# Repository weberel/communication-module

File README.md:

# ecoTrace Communication Module

> ## 🚧 HARDWARE VALIDATED, APPLICATION NOT YET - read this
> As of the **2026-08-06/07** bring-up campaign the **board is fully validated on
> real hardware**: both charge inputs (USB and solar, incl. VINDPM/MPPT control),
> cellular, WiFi, all I2C sensors, the SPI flash, deep sleep, and the QON button
> (wake / OTA mode / ship-mode power-off). GPS is the only untested block.
> The `lib/EcoTrace` drivers underneath all of that ran on hardware too.
>
> What has **NOT been exercised end-to-end** is the **`datalogger` application
> itself**: the 5-minute duty cycle, the flash ring log across power loss, MPPT
> tracking over a real day, the twice-daily ThingsBoard upload with clock sync,
> and watchdog/crash recovery. It compiles and boots; treat it as a scaffold to
> validate, not as proven.
>
> Full breakdown, including the measured numbers: [`docs/testing-status.md`](docs/testing-status.md).

Firmware and board-support for the **ecoTrace Communication Module** - a small,
battery- and solar-powered ESP32-C6 board with an LTE modem, built for **logging
data remotely** from the field.

This repo gives you a ready-to-run **datalogger** plus a library of drop-in
**functions for every peripheral** on the board, so you can fork the logger and add
whatever you need. It is the starting point for anyone (students, collaborators)
picking up the board.

> ⚠️ **Read [`docs/hardware-errata.md`](docs/hardware-errata.md) before wiring anything.**
> Rev A has a **swapped VIN +/- silkscreen** and other gotchas.

---

## The board at a glance

| | |
|---|---|
| MCU | ESP32-C6-MINI-1 (WiFi / BLE / 802.15.4, native USB Serial/JTAG) |
| Power / charging | **BQ25792** buck-boost charger + PMIC - USB, solar (MPPT), LiPo, 16-bit ADC |
| Cellular | **SIMCom A7672E-LASE** LTE Cat-1 modem (+ internal GNSS, untested) |
| Sensors (optional) | SC7A20 accelerometer, LTR-303ALS ambient light |
| Storage | GD25Q128 16 MB SPI NOR flash |
| Security | ATECC608B secure element |
| Inputs | USB-C (power + flashing), SIM slot, battery connector, VIN (solar/DC in) |
| Antennas | u.FL for LTE and GPS |

Board revision: **Rev A, 2026-04-23**. Full KiCad project, schematic PDF, board
renders, and JLCPCB fab files are in [`hardware/`](hardware/).

## What you get

**1. The datalogger** (`src/datalogger/`) - the main application. Every 5-minute
wake it:
- reads the full battery + charger state (BQ25792) and the I2C sensors
  (LTR-303 light, SC7A20 accel, MS5837 pressure + temperature on the hat header),
- runs a solar-management pass: **MPPT** (fractional-Voc + perturb-&-observe on
  VINDPM) to maximise input power, per-day **harvest accounting**, and a
  **weather-adaptive charge target** - good weather caps charging at ~80 % SoC to
  age the LiPo slower, bad weather allows 100 % for reserve,
- appends one 64-byte record to a **ring log on the 16 MB SPI flash**
  (power-loss safe, ~2.5 years of capacity),
- twice a day drains the backlog to **ThingsBoard** in timestamped batches -
  cellular first, **WiFi as backup** - and syncs the wall clock from the network,
- deep-sleeps in between with everything powered down (modem rail, flash,
  sensors, charger ADC); the BQ25792 keeps charging autonomously.

It is a **hackable starting point** - fork it and change whatever you need. To log
your own sensor: extend `LogRecord` in [`record.h`](src/datalogger/record.h) (spare
bytes are reserved), read it in `readSample()` in
[`main.cpp`](src/datalogger/main.cpp), and send it in `recordValues()` in
[`uplink.cpp`](src/datalogger/uplink.cpp). Connect external sensors on the SENSOR
(I2C) or SPI header. Tune the duty cycle / charge profile / MPPT / weather
thresholds in [`config.h`](src/datalogger/config.h).

**2. The driver library** (`lib/EcoTrace/`) - ready-to-call functions for every part
on the board. Pull in only what you need. Full list: [`docs/api-reference.md`](docs/api-reference.md).

| Driver | Covers | Status |
|--------|--------|--------|
| `BQ25792` | charging (USB + solar), ADC, status, faults, MPPT/VINDPM | ✅ full, datasheet-accurate |
| `ModemA7672` | LTE power/AT, SIM, registration, GPRS, HTTP GET/POST, time | ✅ full (GPS = stub) |
| `LTR303` | ambient light (CH0/CH1, lux) - datalogger's example sensor | ✅ |
| `SC7A20` | accelerometer (X/Y/Z mg) | ✅ |
| `ExtFlash` | GD25Q128 read/erase/program, power-down | ✅ (full 16 MB) |
| `MS5837` | MS5837-02BA barometer (pressure, temperature, altitude) | ✅ |
| `ATECC608B` | secure element presence/wake | 🔹 thin (crypto via CryptoAuthLib) |
| `EcoTraceBoard` | safe init, I2C/SPI bring-up, deep sleep | ✅ |

**3. The board self-test** (`src/functionality_test/`) - probes every device and
prints a `PASS / FAIL / SKIP` report. Run it first on a new board.

## Toolchain

**VS Code + PlatformIO + Arduino-ESP32.** Reproducible builds, a real editor, the
Arduino library ecosystem, and full ESP-IDF APIs underneath when needed. See
[`docs/getting-started.md`](docs/getting-started.md).

The ESP32-C6 needs arduino-esp32 v3+, which the official PlatformIO platform does not
ship yet - this project pins the [pioarduino](https://github.com/pioarduino/platform-espressif32)
fork (version `53.03.13`) in `platformio.ini`. Don't unpin it.

## Quick start

```bash
# 1. open this folder in VS Code with the PlatformIO extension installed
# 2. plug the board in over USB-C (keep a battery connected -- see errata)
# 3. check the board is healthy:
pio run -e functionality_test -t upload && pio device monitor

# 4. set your SIM APN + upload URL, then run the logger:
cp lib/EcoTrace/secrets.example.h lib/EcoTrace/secrets.h   # then edit it
pio run -e datalogger -t upload && pio device monitor

# 5. reflash over WiFi later (bench convenience): press the QON button 3x
#    (board joins WiFi, blinks once per second, prints its IP on serial), then:
pio run -e datalogger        # build the new image
curl -F "image=@.pio/build/datalogger/firmware.bin" http://<board-ip>/update
#    (espota / `pio run -e datalogger_ota -t upload` also exists but its UDP
#     handshake proved unreliable on real networks -- prefer the curl path)
```

Without a `POST_URL` in `secrets.h` the datalogger runs in bench mode: it samples and
prints over serial but does not transmit.

## Layout

```
lib/EcoTrace/      board support: pin map + drivers (the reusable core)
  ecotrace_pins.h    single source of truth for the pin map
  EcoTraceBoard.*    safe init, I2C/SPI bring-up, deep-sleep helper
  BQ25792.*          charger / PMIC (hand-written, datasheet-accurate)
  ModemA7672.*       LTE modem (hand-written AT stack)
  LTR303.* SC7A20.* ATECC608B.* ExtFlash.*   peripheral drivers
  secrets.example.h  copy to secrets.h and fill in (gitignored)
src/
  datalogger/        the main application
    config.h           duty cycle, charge profile, MPPT, weather, upload tunables
    record.h           the 64-byte on-flash log record (+ CRC)
    flash_log.*        power-loss-safe ring log on the 16 MB SPI flash
    solar.*            MPPT + harvest tracking + weather-adaptive charge target
    uplink.*           ThingsBoard upload: cellular first, WiFi backup, clock sync
    main.cpp           the wake/sample/sleep cycle
  functionality_test/  board bring-up self-test
docs/              getting started, pinout, errata, api reference, testing status
hardware/          KiCad project + exports
```

## Related

- `functionality_test_arduino` - the original bring-up test this repo grew from.
- `bms_stove` - an ESP-IDF application on this hardware (remote battery/stove
  datalogger), a reference for a full deployment.

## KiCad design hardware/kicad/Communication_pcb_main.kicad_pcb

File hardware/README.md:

# Hardware

The KiCad design and manufacturing outputs for the ecoTrace Communication Module
(Rev A, 2026-04-23) are included here so you don't need Drive access.

```
hardware/
  kicad/         KiCad project - open Communication_pcb_main.kicad_pro in KiCad
    Communication_pcb_main.kicad_pro / .kicad_pcb / .kicad_sch
    mcu.kicad_sch  power_mgmt.kicad_sch  simcom.kicad_sch   (schematic sheets)
    jlcpcb/        fab outputs: gerbers, drill, BOM, CPL, GERBER-*.zip
  exports/       viewable without KiCad:
    Communication_pcb_main-schematic.pdf
    board-top.png  board-bottom.png   (3D renders)
```

## No KiCad? Start here

- **Schematic:** `exports/Communication_pcb_main-schematic.pdf`. Sheets: `mcu`,
  `power_mgmt`, `simcom`. The **power_mgmt** sheet (BQ25792) is the one to know: it
  defines the charging path, VSYS, the NTC (TS) network (note the errata), and the
  ACDRV FET gating for USB vs solar inputs.
- **Board:** `exports/board-top.png` / `board-bottom.png`.

## Fabrication

`kicad/jlcpcb/` holds a ready-to-order set (gerbers, drill, BOM, CPL, and a zipped
gerber bundle) targeted at JLCPCB. Re-export from KiCad if you change the board.

This is the **current 4-layer** version of the board (F.Cu / In1 / In2 / B.Cu). An
older 2-layer design also exists on the shared drive; it is not included here.

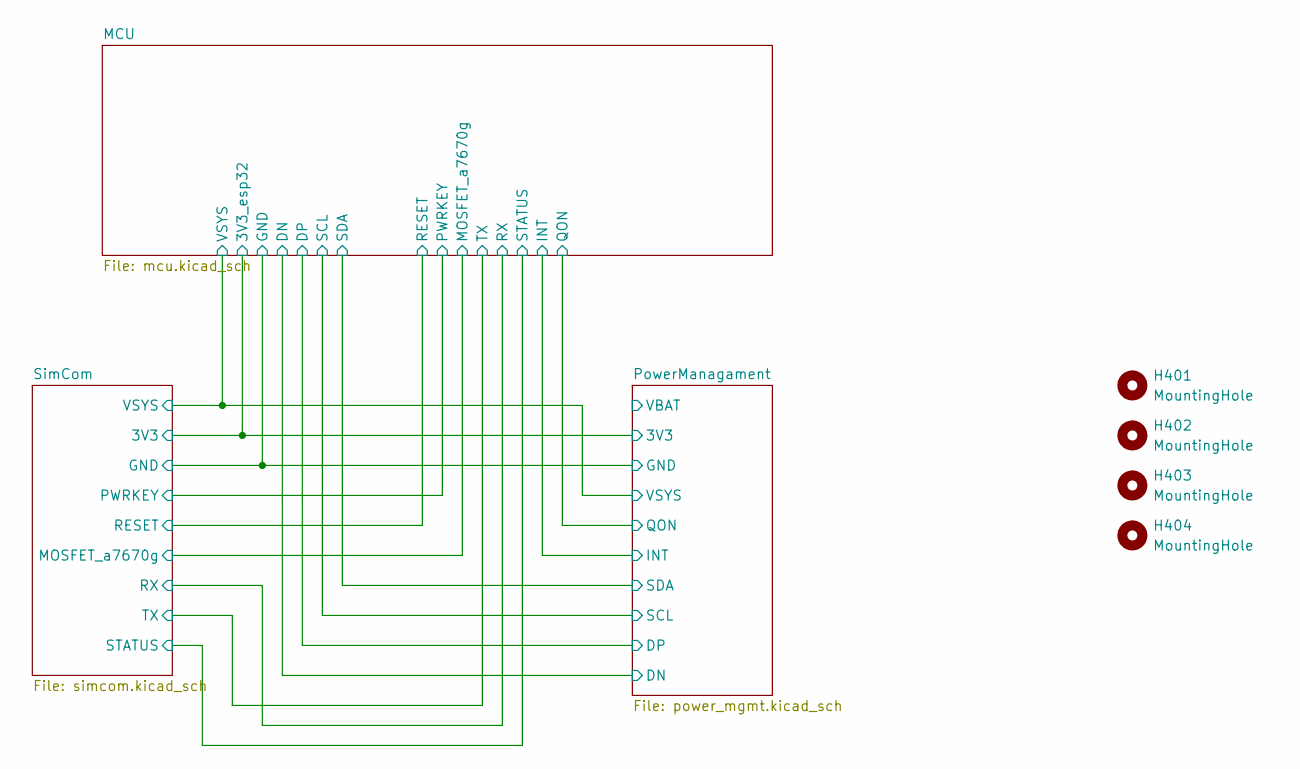
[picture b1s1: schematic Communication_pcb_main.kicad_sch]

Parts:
H401, H403: MountingHole; MountingHole_2.2mm_M2_ISO14580_Pad
H402, H404: MountingHole; Slot_2.2mm_M2_ISO14580_Pad

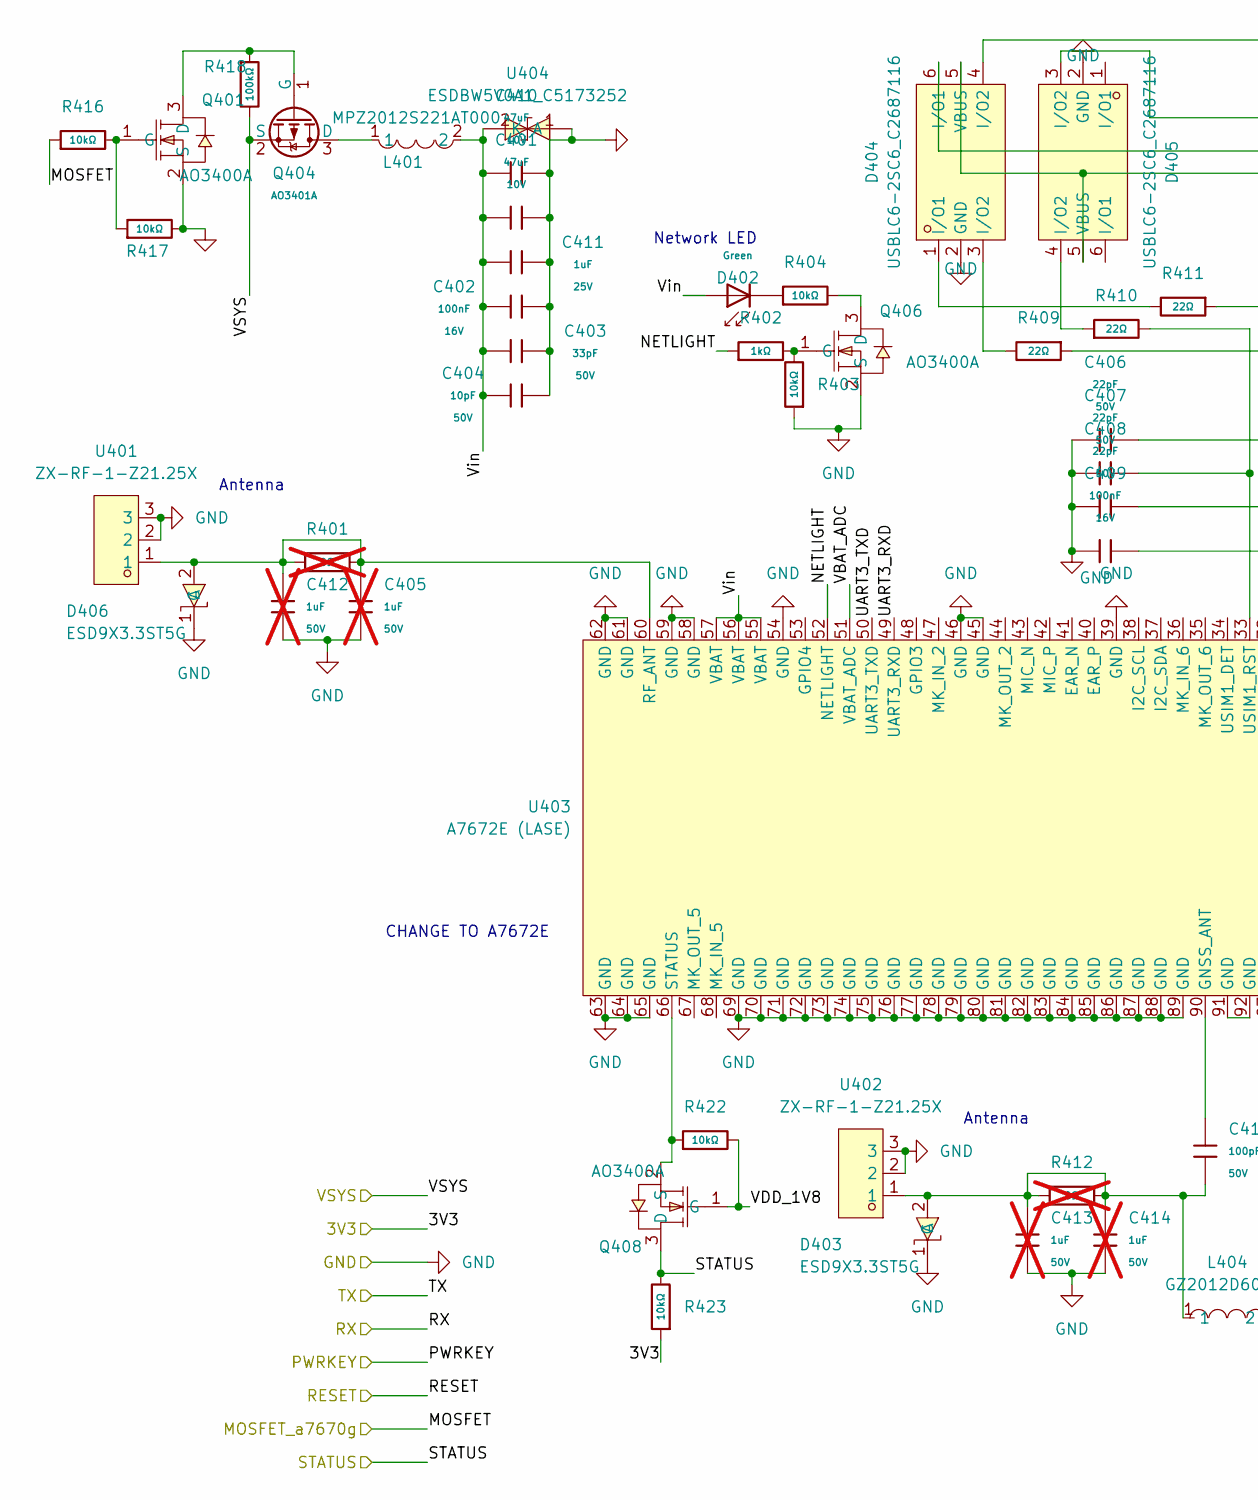
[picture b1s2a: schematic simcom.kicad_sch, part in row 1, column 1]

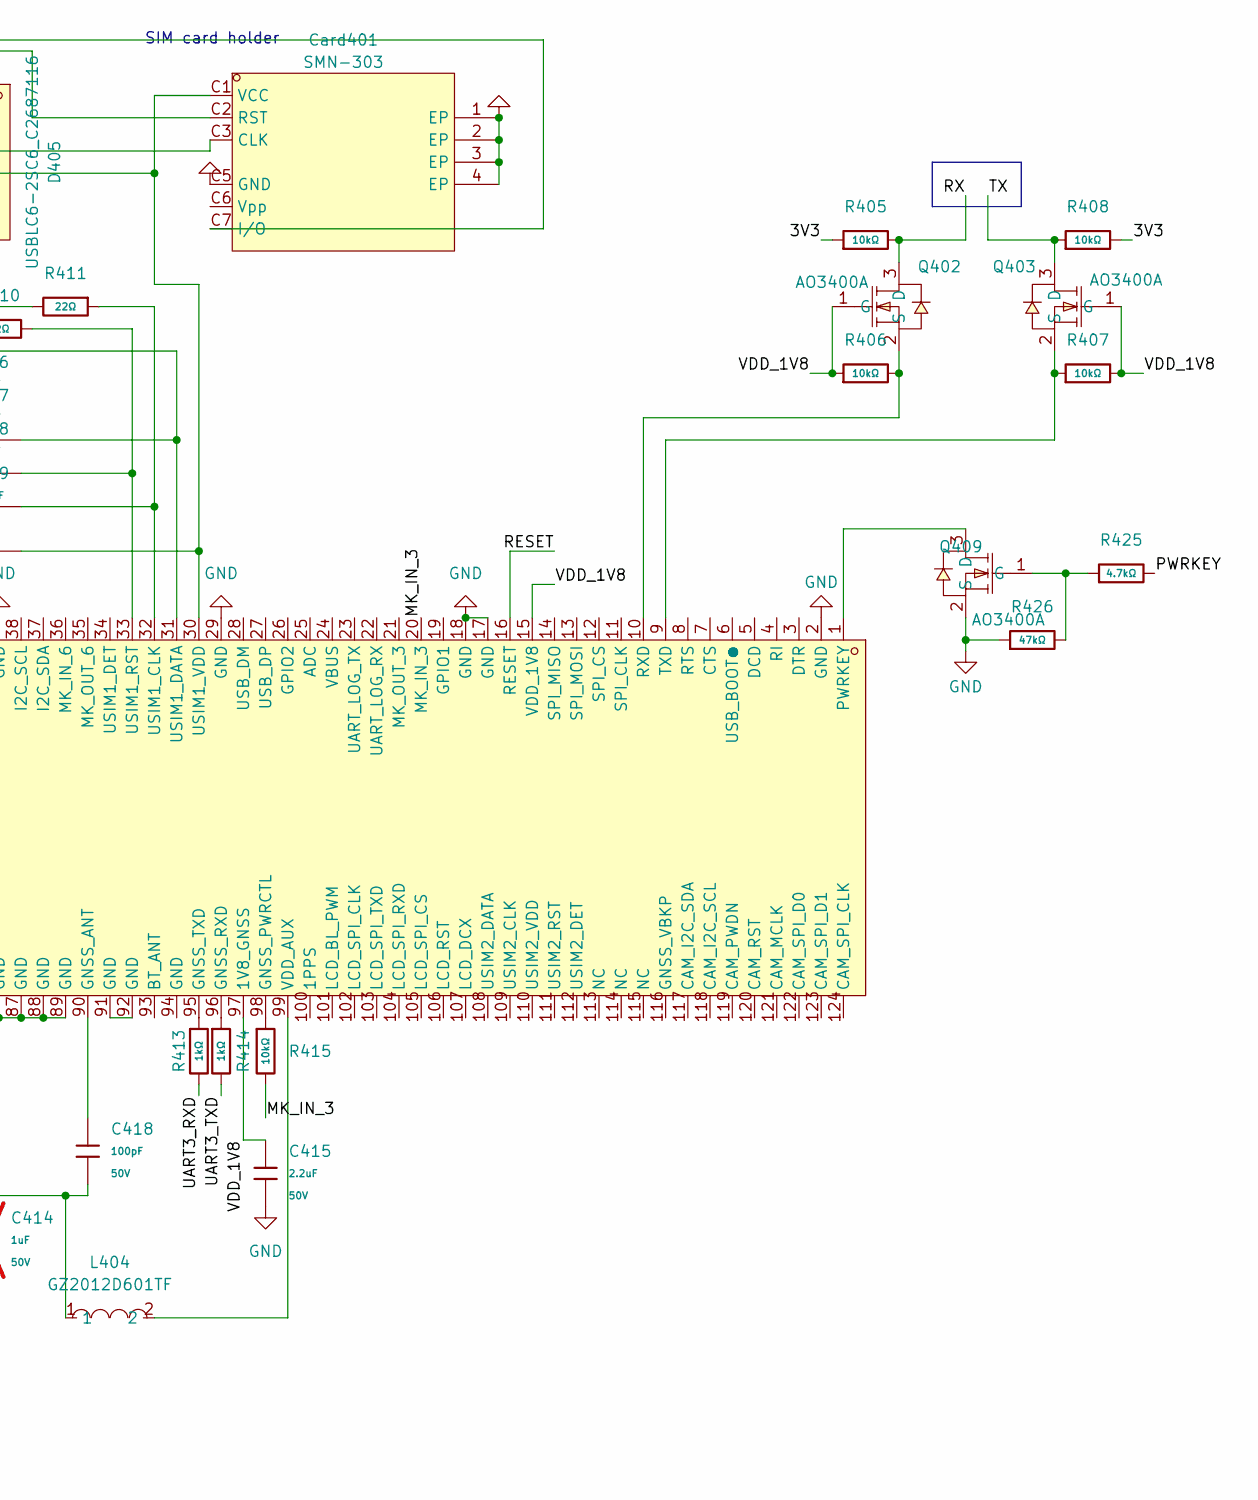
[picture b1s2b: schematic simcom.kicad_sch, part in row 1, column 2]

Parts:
C401, C410: 47uF; C_1206; Voltage Rated 10V; Tolerance ±20%; Part CL31A476MPHNNNE; LCSC C96123
C402, C409: 100nF; C_0402; Voltage Rated 16V; Tolerance ±10%; Part CL05B104KO5NNNC; LCSC C1525
C403: 33pF; C_0402; Voltage Rated 50V; Tolerance ±5%; Part 0402CG330J500NT; LCSC C1562
C404: 10pF; C_0402; Voltage Rated 50V; Tolerance ±5%; Part CL05C100JB5NNNC; LCSC C32949
C405, C412, C413, C414: 1uF; C_0805; Voltage Rated 50V; Tolerance ±10%; Part CL21B105KBFNNNE; LCSC C28323; not fitted
C406, C407, C408: 22pF; C_0402; Voltage Rated 50V; Tolerance ±5%; Part 0402CG220J500NT; LCSC C1555
C411: 1uF; C_0402; Voltage Rated 25V; Tolerance ±10%; Part CL05A105KA5NQNC; LCSC C52923
C415: 2.2uF; C_0805; Voltage Rated 50V; Tolerance ±10%; Part CL21A225KBQNNNE; LCSC C377773
C418: 100pF; C_0805; Voltage Rated 50V; Tolerance ±5%; Part CL21C101JBANNNC; LCSC C1790
Card401: SMN-303; SIM-SMD_SMN-305; LCSC Part C266890
D402: Green; D_0805; Part KT-0805G; LCSC C2297
D403, D406: ESD9X3.3ST5G; SOD-923_L0.8-W0.6-LS1.0-RD; MPN ESD9X3.3ST5G; LCSC Part C130456
D404, D405: USBLC6-2SC6_C2687116; SOT-23-6_L2.9-W1.6-P0.95-LS2.8-BL; LCSC Part C2687116
L401: MPZ2012S221AT000; L0805; LCSC Part C76818
L404: GZ2012D601TF; L0805; MPN GZ2012D601TF; LCSC Part C1017
Q401, Q402, Q403, Q406, Q408, Q409: AO3400A; SOT-23-3_L2.9-W1.3-P1.90-LS2.4-BR; MPN AO3400A; LCSC Part C20917
Q404: AO3401A; Q_SOT-23; Part AO3401A; LCSC C15127
R401, R412: 0Ω; R_0805; Overload Voltage (Max) 150V; Tolerance ±1%; Part 0805W8F0000T5E; LCSC C17477; not fitted
R402, R413, R414: 1kΩ; R_0402; Overload Voltage (Max) 50V; Tolerance ±1%; Part 0402WGF1001TCE; LCSC C11702
R403, R404, R405, R406, R407, R408, R415, R416, R417, R422, R423: 10kΩ; R_0402; Overload Voltage (Max) 50V; Tolerance ±1%; Part 0402WGF1002TCE; LCSC C25744
R409, R410, R411: 22Ω; R_0402; Overload Voltage (Max) 50V; Tolerance ±1%; Part 0402WGF220JTCE; LCSC C25092
R418: 100kΩ; R_0402; Overload Voltage (Max) 50V; Tolerance ±1%; Part 0402WGF1003TCE; LCSC C25741
R425: 4.7kΩ; R_0402; Overload Voltage (Max) 50V; Tolerance ±1%; Part 0402WGF4701TCE; LCSC C25900
R426: 47kΩ; R_0402; Overload Voltage (Max) 50V; Tolerance ±1%; Part 0402WGF4702TCE; LCSC C25792
U401, U402: ZX-RF-1-Z21.25X; IPEX-SMD_3P-L2.6-W2.6-LS3.0_YUANDI_RF-001; LCSC Part C7426714
U403: A7672E (LASE); LGA-124_L24.0-W24.0-P1.0-A7670C-LASS; LCSC Part C6116733
U404: ESDBW5V0A1_C5173252; X1-DFN1006-2_L1.0-W0.6-P0.65-BI; LCSC Part C5173252

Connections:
/MCU/3V3_esp32: R405.1, R408.2, R423.1; also elsewhere on the board
/MCU/MOSFET_a7670g: R416.1; also elsewhere on the board
/MCU/PWRKEY: R425.2; also elsewhere on the board
/MCU/RESET: U403.16 (RESET)
/MCU/RX: Q402.3 (D), R405.2; also elsewhere on the board
/MCU/STATUS: Q408.3 (D), R423.2; also elsewhere on the board
/MCU/TX: Q403.3 (D), R408.1; also elsewhere on the board
/MCU/VSYS: Q404.2 (S), R418.2; also elsewhere on the board
/SimCom/MK_IN_3: R415.2, U403.20 (MK_IN_3)
/SimCom/NETLIGHT: R402.1, U403.52 (NETLIGHT)
/SimCom/UART3_RXD: R413.2, U403.49 (UART3_RXD)
/SimCom/UART3_TXD: R414.2, U403.50 (UART3_TXD)
/SimCom/VBAT_ADC: U403.51 (VBAT_ADC)
/SimCom/VDD_1V8: C415.2, Q402.1 (G), Q403.1 (G), Q408.1 (G), R406.1, R407.2, R422.2, U403.15 (VDD_1V8), U403.97 (1V8_GNSS)
/SimCom/Vin: C401.1, C402.1, C403.1, C404.1, C410.1, C411.1, D402.2, L401.2, U403.55 (VBAT), U403.56 (VBAT), U403.57 (VBAT), U404.2 (A)
GND: C401.2, C402.2, C403.2, C404.2, C405.2, C406.1, C407.1, C408.1, C409.1, C410.2, C411.2, C412.2, C413.2, C414.2, C415.1, Card401.1 (EP), Card401.2 (EP), Card401.3 (EP), Card401.4 (EP), Card401.C5 (GND), D403.1 (C), D404.2 (GND), D405.2 (GND), D406.1 (C), Q401.2 (S), Q406.2 (S), Q409.2 (S), R403.1, R417.2, R426.1, U401.2, U401.3, U402.2, U402.3, U403.2 (GND), U403.17 (GND), U403.18 (GND), U403.29 (GND), U403.39 (GND), U403.45 (GND), U403.46 (GND), U403.54 (GND), U403.58 (GND), U403.59 (GND), U403.61 (GND), U403.62 (GND), U403.63 (GND), U403.64 (GND), U403.65 (GND), U403.69 (GND), U403.70 (GND), U403.71 (GND), U403.72 (GND), U403.73 (GND), U403.74 (GND), U403.75 (GND), U403.76 (GND), U403.77 (GND), U403.78 (GND), U403.79 (GND), U403.80 (GND), U403.81 (GND), U403.82 (GND), U403.83 (GND), U403.84 (GND), U403.85 (GND), U403.86 (GND), U403.87 (GND), U403.88 (GND), U403.89 (GND), U404.1 (K); also elsewhere on the board
unnamed: Card401.C3 (CLK), D404.6 (I/O1)
unnamed: Card401.C7 (I/O), D404.4 (I/O2)
unnamed: Card401.C2 (RST), D405.3 (I/O2)
unnamed: C409.2, Card401.C1 (VCC), D404.5 (VBUS), D405.5 (VBUS), U403.30 (USIM1_VDD)
unnamed: D402.1, R404.1
unnamed: C413.1, C414.1, C418.1, D403.2 (A), L404.1, R412.1, R412.2, U402.1
unnamed: D404.1 (I/O1), R411.2
unnamed: D404.3 (I/O2), R409.2
unnamed: D405.4 (I/O2), R410.1
unnamed: C405.1, C412.1, D406.2 (A), R401.1, R401.2, U401.1, U403.60 (RF_ANT)
unnamed: Q401.3 (D), Q404.1 (G), R418.1
unnamed: Q401.1 (G), R416.2, R417.1
unnamed: Q402.2 (S), R406.2, U403.10 (RXD)
unnamed: Q403.2 (S), R407.1, U403.9 (TXD)
unnamed: L401.1, Q404.3 (D)
unnamed: Q406.3 (D), R404.2
unnamed: Q406.1 (G), R402.2, R403.2
unnamed: Q408.2 (S), R422.1, U403.66 (STATUS)
unnamed: Q409.3 (D), U403.1 (PWRKEY)
unnamed: Q409.1 (G), R425.1, R426.2
unnamed: U403.91 (GND), U403.92 (GND)
unnamed: C418.2, U403.90 (GNSS_ANT)
unnamed: R415.1, U403.98 (GNSS_PWRCTL)
unnamed: R414.1, U403.96 (GNSS_RXD)
unnamed: R413.1, U403.95 (GNSS_TXD)
unnamed: C408.2, R411.1, U403.32 (USIM1_CLK)
unnamed: C406.2, R409.1, U403.31 (USIM1_DATA)
unnamed: C407.2, R410.2, U403.33 (USIM1_RST)
unnamed: L404.2, U403.99 (VDD_AUX)

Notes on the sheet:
Antenna
Network LED
CHANGE TO A7672E
SIM card holder

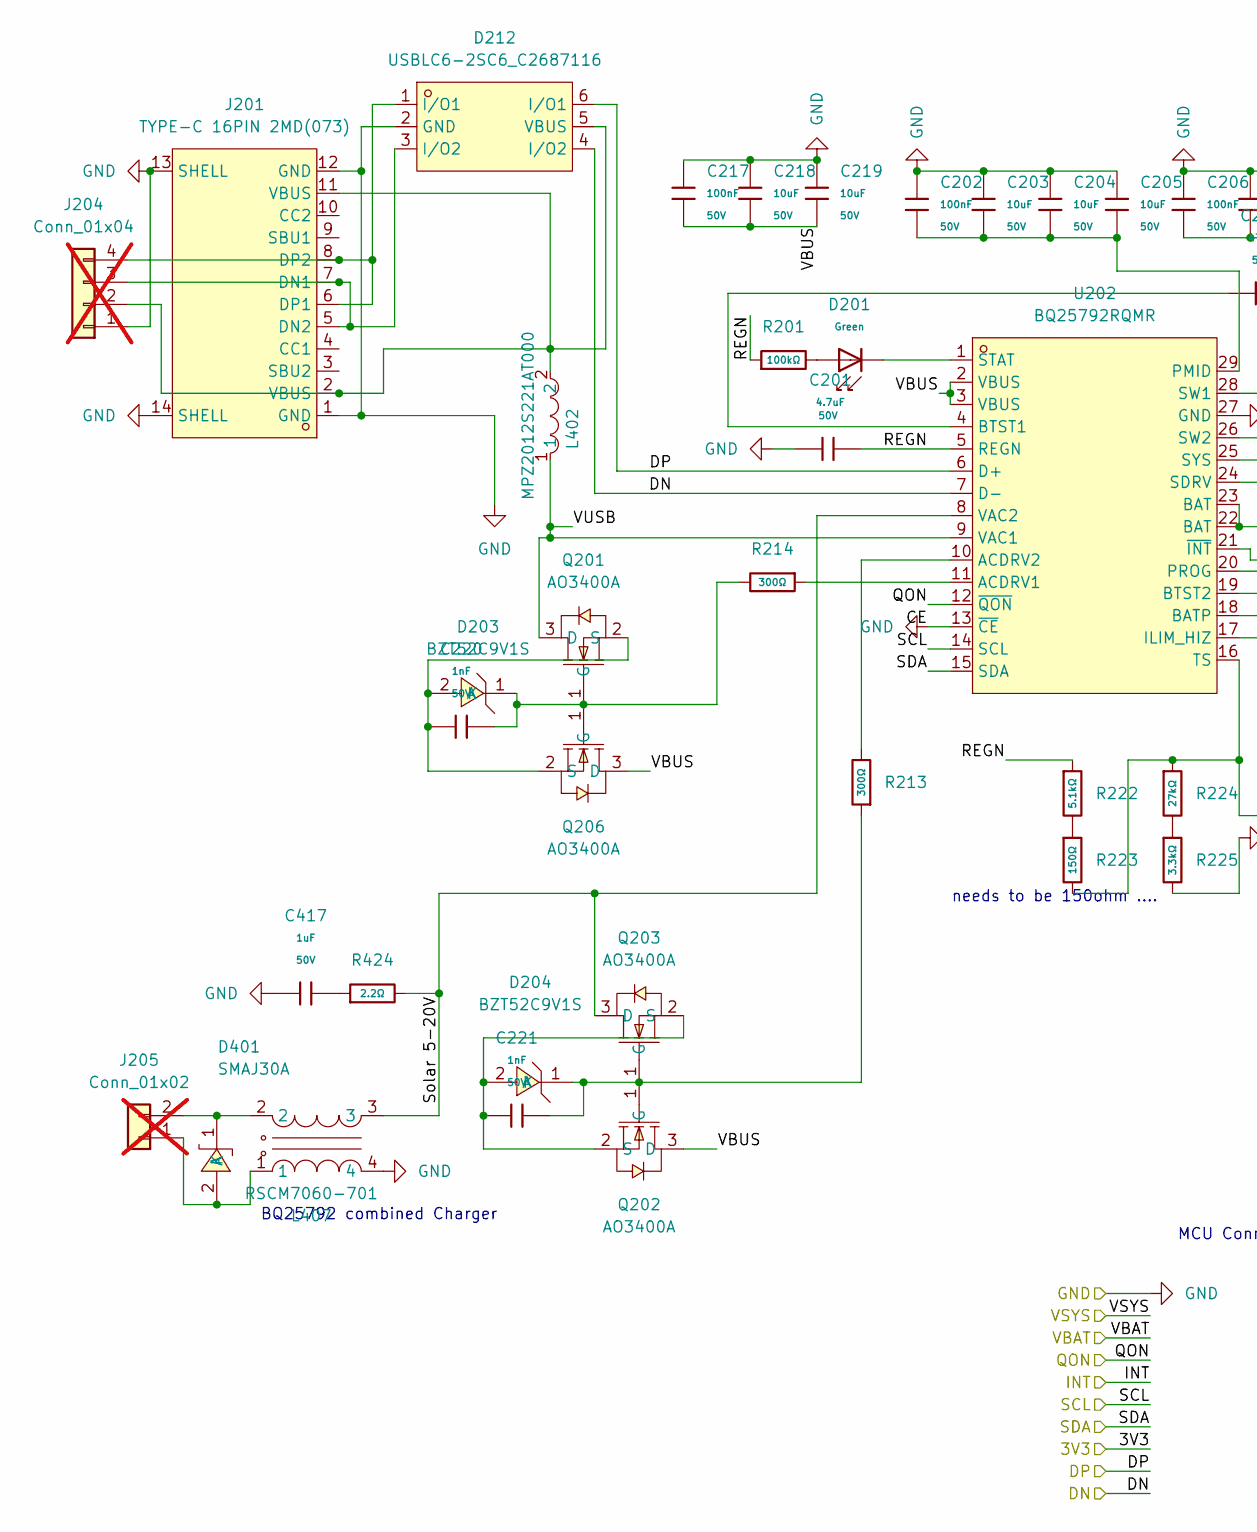
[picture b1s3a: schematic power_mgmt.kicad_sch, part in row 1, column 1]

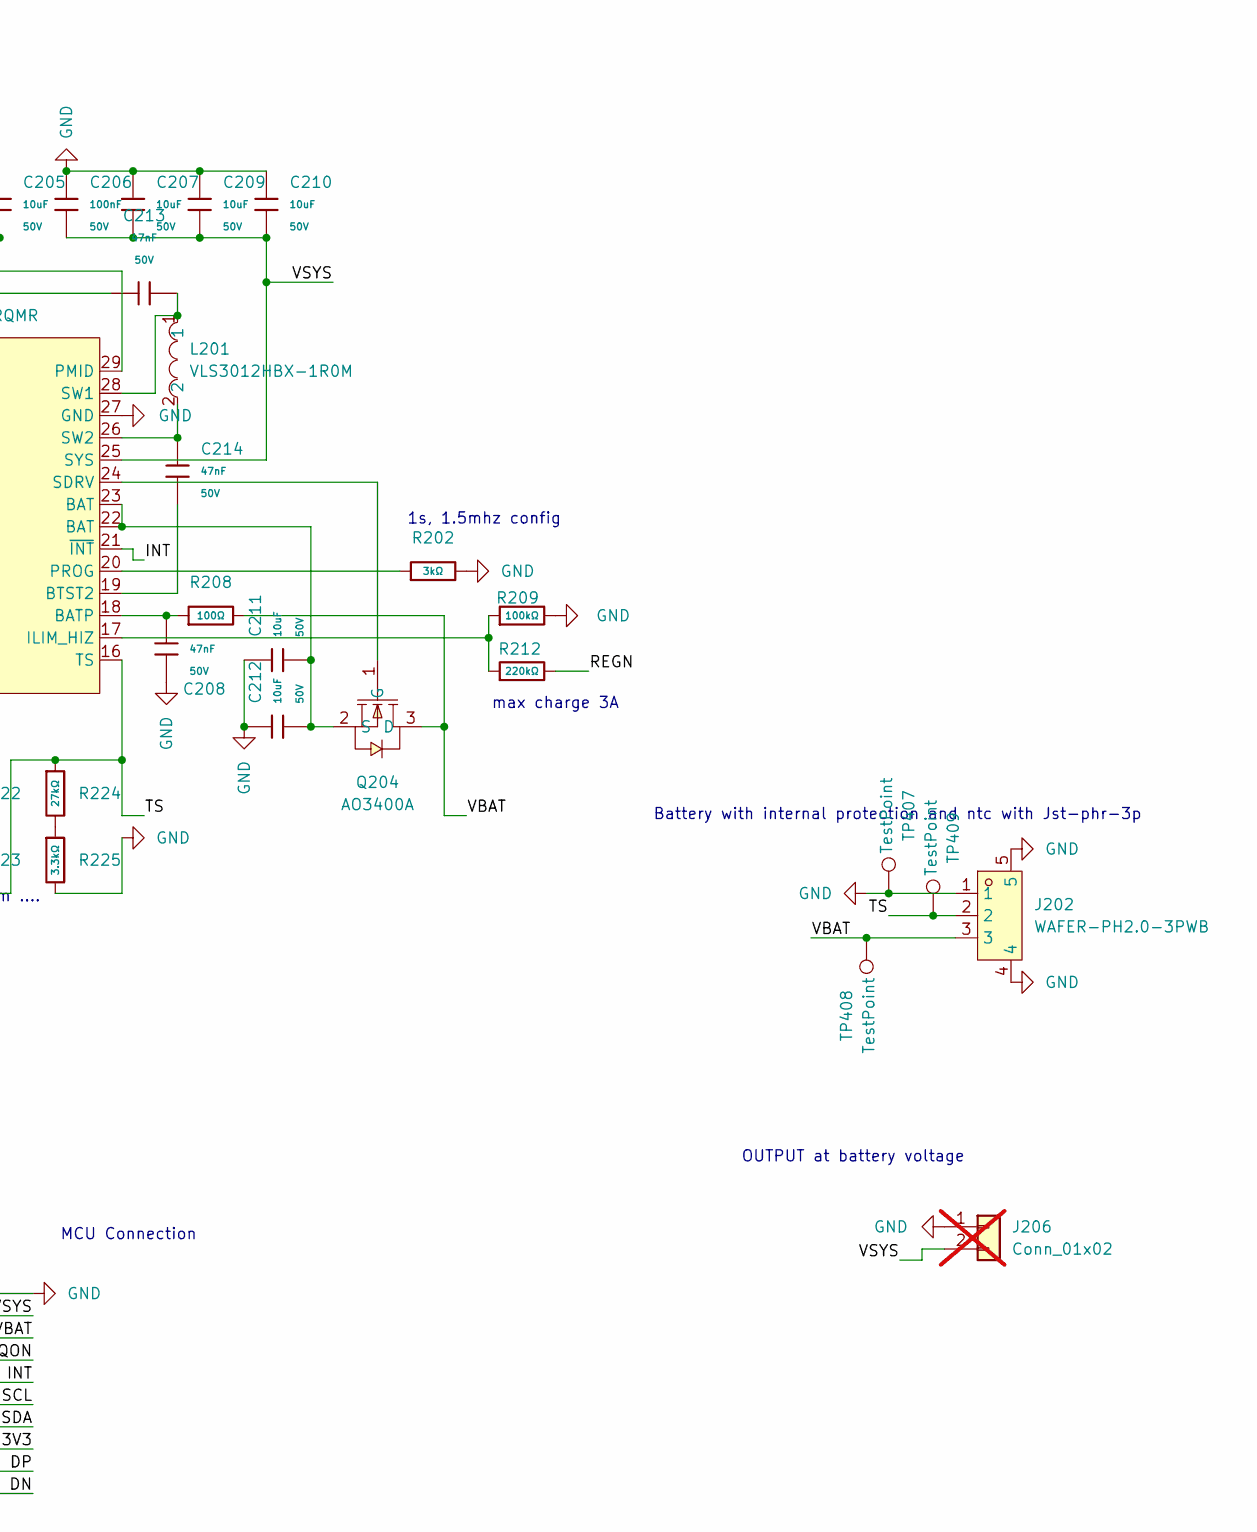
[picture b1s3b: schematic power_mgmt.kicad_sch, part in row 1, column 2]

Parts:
C201: 4.7uF; C_1206; Voltage Rated 50V; Tolerance ±10%; Part 1206B475K500NT; LCSC C29823
C202, C206, C217: 100nF; C_0603; Voltage Rated 50V; Tolerance ±10%; Part CC0603KRX7R9BB104; LCSC C14663
C203, C204, C205, C207, C209, C210, C211, C212, C218, C219: 10uF; C_1206; Voltage Rated 50V; Tolerance ±10%; Part CL31A106KBHNNNE; LCSC C13585
C208, C213, C214: 47nF; C_0603; Voltage Rated 50V; Tolerance ±10%; Part CL10B473KB8NNNC; LCSC C1622
C220, C221: 1nF; C_0402; Voltage Rated 50V; Tolerance ±10%; Part 0402B102K500NT; LCSC C1523
C417: 1uF; C_0603; Voltage Rated 50V; Tolerance ±10%; Part CL10A105KB8NNNC; LCSC C15849
D201: Green; D_0805; Part KT-0805G; LCSC C2297
D203, D204: BZT52C9V1S; SOD-323_L1.8-W1.3-LS2.5-RD; LCSC Part C22614
D212: USBLC6-2SC6_C2687116; SOT-23-6_L2.9-W1.6-P0.95-LS2.8-BL; LCSC Part C2687116
D401: SMAJ30A; SMA_L4.3-W2.6-LS5.2-RD; MPN SMAJ30A; LCSC Part C10767
J201: TYPE-C 16PIN 2MD(073); USB-C-SMD_TYPE-C-6PIN-2MD-073; LCSC Part C2765186
J202: WAFER-PH2.0-3PWB; CONN-SMD_3P-P2.00_XUNPU_WAFER-PH2.0-3PWB; LCSC Part C3029441
J204: Conn_01x04; custom_01x04_2.54; not fitted
J205, J206: Conn_01x02; custom_1x02_2.54; not fitted
L201: VLS3012HBX-1R0M; IND-SMD_L3.0-W3.0_VLS3012CX; LCSC Part C404493
L402: MPZ2012S221AT000; L0805; LCSC Part C76818
L407: RSCM7060-701; FILTER-SMD_4P-L7.0-W6.0-P3.00-TL; MPN RSCM7060-701; LCSC Part C32712963
Q201, Q202, Q203, Q204, Q206: AO3400A; SOT-23-3_L2.9-W1.3-P1.90-LS2.4-BR; LCSC Part C20917
R201, R209: 100kΩ; R_0402; Overload Voltage (Max) 50V; Tolerance ±1%; Part 0402WGF1003TCE; LCSC C25741
R202: 3kΩ; R_0603; Overload Voltage (Max) 75V; Tolerance ±1%; Part 0603WAF3001T5E; LCSC C4211
R208: 100Ω; R_0603; Overload Voltage (Max) 75V; Tolerance ±1%; Part 0603WAF1000T5E; LCSC C22775
R212: 220kΩ; R_0603; Overload Voltage (Max) 75V; Tolerance ±1%; Part 0603WAF2203T5E; LCSC C22961
R213, R214: 300Ω; R_0805; Overload Voltage (Max) 150V; Tolerance ±1%; Part 0805W8F3000T5E; LCSC C17617
R222: 5.1kΩ; R_0402; Overload Voltage (Max) 50V; Tolerance ±1%; Part 0402WGF5101TCE; LCSC C25905
R223: 150Ω; R_0603; Overload Voltage (Max) 75V; Tolerance ±1%; Part 0603WAF1500T5E; LCSC C22808
R224: 27kΩ; R_0603; Overload Voltage (Max) 75V; Tolerance ±1%; Part 0603WAF2702T5E; LCSC C22967
R225: 3.3kΩ; R_0402; Overload Voltage (Max) 50V; Tolerance ±1%; Part 0402WGF3301TCE; LCSC C25890
R424: 2.2Ω; R_0603; Overload Voltage (Max) 75V; Tolerance ±1%; Part 0603WAF220KT5E; LCSC C22939
TP407, TP408, TP409: TestPoint; TestPoint_Pad_D1.0mm
U202: BQ25792RQMR; QFN-29_L4.0-W4.0-P0.40-TL-BQ25792RQMR; LCSC Part C2862876

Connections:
/MCU/DN: D212.4 (I/O2), U202.7 (D-); also elsewhere on the board
/MCU/DP: D212.6 (I/O1), U202.6 (D+); also elsewhere on the board
/MCU/INT: U202.21 (~INT); also elsewhere on the board
/MCU/QON: U202.12 (~QON); also elsewhere on the board
/MCU/SCL: U202.14 (SCL); also elsewhere on the board
/MCU/SDA: U202.15 (SDA); also elsewhere on the board
/MCU/VSYS: C206.2, C207.2, C209.2, C210.2, J206.2, U202.25 (SYS); also elsewhere on the board
/PowerManagament/REGN: C201.2, R201.1, R212.2, R222.1, U202.5 (REGN)
/PowerManagament/Solar 5-20V: L407.3, Q203.3 (D), R424.2, U202.8 (VAC2)
/PowerManagament/TS: J202.2, R223.2, R224.1, TP409.1 (1_1), U202.16 (TS)
/PowerManagament/VBAT: J202.3, Q204.3 (D), R208.2, TP408.1 (1_1)
/PowerManagament/VBUS: C217.2, C218.2, C219.2, Q202.3 (D), Q206.3 (D), U202.2 (VBUS), U202.3 (VBUS)
/PowerManagament/VUSB: L402.1, Q201.3 (D), U202.9 (VAC1)
GND: C201.1, C202.1, C203.1, C204.1, C205.1, C206.1, C207.1, C208.1, C209.1, C210.1, C211.1, C212.1, C217.1, C218.1, C219.1, C417.1, D212.2 (GND), J201.1 (GND), J201.12 (GND), J201.13 (SHELL), J201.14 (SHELL), J202.1, J202.4, J202.5, J204.1, J206.1, L407.4, R202.2, R209.2, R225.2, TP407.1 (1_1), U202.13 (~CE), U202.27 (GND); also elsewhere on the board
unnamed: C417.2, R424.1
unnamed: D201.2, R201.2
unnamed: C220.1, D203.2 (A), Q201.2 (S), Q206.2 (S)
unnamed: C220.2, D203.1 (K), Q201.1 (G), Q206.1 (G), R214.2
unnamed: C221.1, D204.2 (A), Q202.2 (S), Q203.2 (S)
unnamed: C221.2, D204.1 (K), Q202.1 (G), Q203.1 (G), R213.1
unnamed: D212.5 (VBUS), J201.2 (VBUS), J201.11 (VBUS), J204.2, L402.2
unnamed: D401.2 (A), J205.1, L407.1
unnamed: D401.1 (K), J205.2, L407.2
unnamed: D212.3 (I/O2), J201.5 (DN2), J201.7 (DN1), J204.3
unnamed: D212.1 (I/O1), J201.6 (DP1), J201.8 (DP2), J204.4
unnamed: Q204.1 (G), U202.24 (SDRV)
unnamed: C211.2, C212.2, Q204.2 (S), U202.22 (BAT), U202.23 (BAT)
unnamed: R222.2, R223.1
unnamed: R224.2, R225.1
unnamed: R214.1, U202.11 (ACDRV1)
unnamed: R213.2, U202.10 (ACDRV2)
unnamed: C208.2, R208.1, U202.18 (BATP)
unnamed: C213.1, U202.4 (BTST1)
unnamed: C214.2, U202.19 (BTST2)
unnamed: R209.1, R212.1, U202.17 (ILIM_HIZ)
unnamed: C202.2, C203.2, C204.2, C205.2, U202.29 (PMID)
unnamed: R202.1, U202.20 (PROG)
unnamed: D201.1, U202.1 (STAT)
unnamed: C213.2, L201.1, U202.28 (SW1)
unnamed: C214.1, L201.2, U202.26 (SW2)

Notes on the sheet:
MCU Connection
max charge 3A
1s, 1.5mhz config
Battery with internal protection and ntc with Jst-phr-3p
OUTPUT at battery voltage
BQ25792 combined Charger
needs to be 150ohm ....
